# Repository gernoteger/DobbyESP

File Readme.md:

# About
DobbyESP is my own ESP8266 based IoT application for controlling things.

The name is inspired by [Dobby, the houself](http://harrypotter.wikia.com/wiki/Dobby) from Harry Potter: serves behind the scenes, but eventually develops a life on its own.

# Requirements
(mostly not yet implemented)
* [ ] enable maintainance without physical access
* [ ] Robust Wifi configuration
* [ ] OTA Updates
* [ ] Admin WebInterface
* [ ] Basic security
* [ ] MQTT for interfacing with OpenHab and crowd control
* [ ] OTA logging
* Devices + sensors
 * [ ] roller blinds / sunblinds
 * [ ] sprinkler with rain sensor
 * [ ] anything that can be switched on or off
 * [ ] Room Heating control & sensing
* make it publicly available, therefore no private acess data must be stored anywhere in version controlled files

 Since the ESP8266 is a Wifi-Only system, it doesn't lend itself well to battery powered operation; this is subject to future research
 
# Architecture

## Software Stack
* [Sming Framework](https://github.com/anakod/Sming "Sming on github")
* [rBoot] (https://github.com/raburton/esp8266 "rBoot on github") for OTA with big flash layout
* spiffs for saving connection information. I originally intended to use the original [xlfe] (https://github.com/xlfe/spiffy "original spiffy") repo; I noticed that the changes needed for Sming are not yet there, so I used [kireefco's fork] (https://github.com/kireevco/spiffy)
* and of course Espressif's SDK, currently V1.2
* Toolchain using chocolatey from sming

## Hardware

* ESP-12 and ESP-07: 4MBit/1MBit Flash, plenty of pins available, including the ADC
* Line powered: off-the-shelf USB Power modules with linear 3.3V controller
* Use Arduino relais modules to switch line: 5V form USB above come in handy, can be controlled with 3,3V from ESP
* as little as possible else

## Project Layout
The TopLevel Project contains all dependencies as git submodules, plus DobbyESP's base directory. 

# Build targets

make ...

* clean
* all

make -f Makefile-sming.mk ...
* sming-clean
* sming-all

* rboot-stuff

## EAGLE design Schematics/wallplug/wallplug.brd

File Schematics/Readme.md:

# Schematics

currently eaglepcb formatted

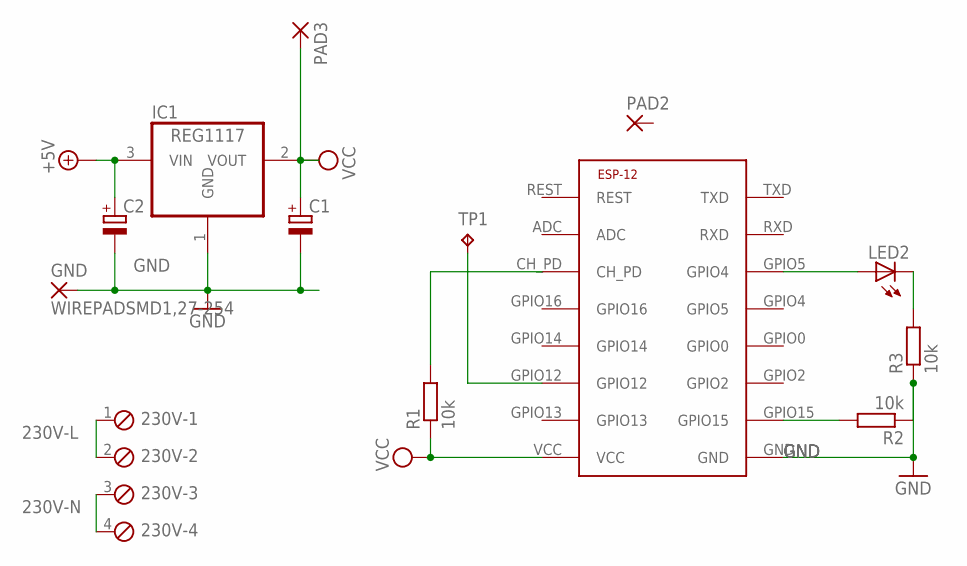
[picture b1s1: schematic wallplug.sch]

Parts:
230V: MPT4; 4POL254
C1, C2: CPOL-EUSMCC; SMC_C
ESP1: ESP-12ESP-12; ESP-12
GND: WIREPADSMD1,27-254; SMD1,27-2,54
IC1: REG1117; SOT223
LED2: LED_ESML0603; LED_SML0603
PAD2: 1,6/0,9
PAD3: SMD5; SMD2,54-5,08
R1, R2, R3: 10k; M0805; MPN LD1117S33TR
TP1: TPB1,27; B1,27

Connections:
230V-L: 230V.1, 230V.2
230V-N: 230V.3, 230V.4
+5V: C2.+, IC1.3 (VIN)
GND: C1.-, C2.-, ESP1.GND, GND.1, IC1.1 (GND), R2.1, R3.1
unnamed: ESP1.CH_PD, R1.2
unnamed: ESP1.GPIO12, TP1.TP
unnamed: ESP1.GPIO15, R2.2
unnamed: ESP1.GPIO5 (GPIO4), LED2.A
unnamed: LED2.C, R3.2
VCC: C1.+, ESP1.VCC, IC1.2 (VOUT), PAD3.1, R1.1

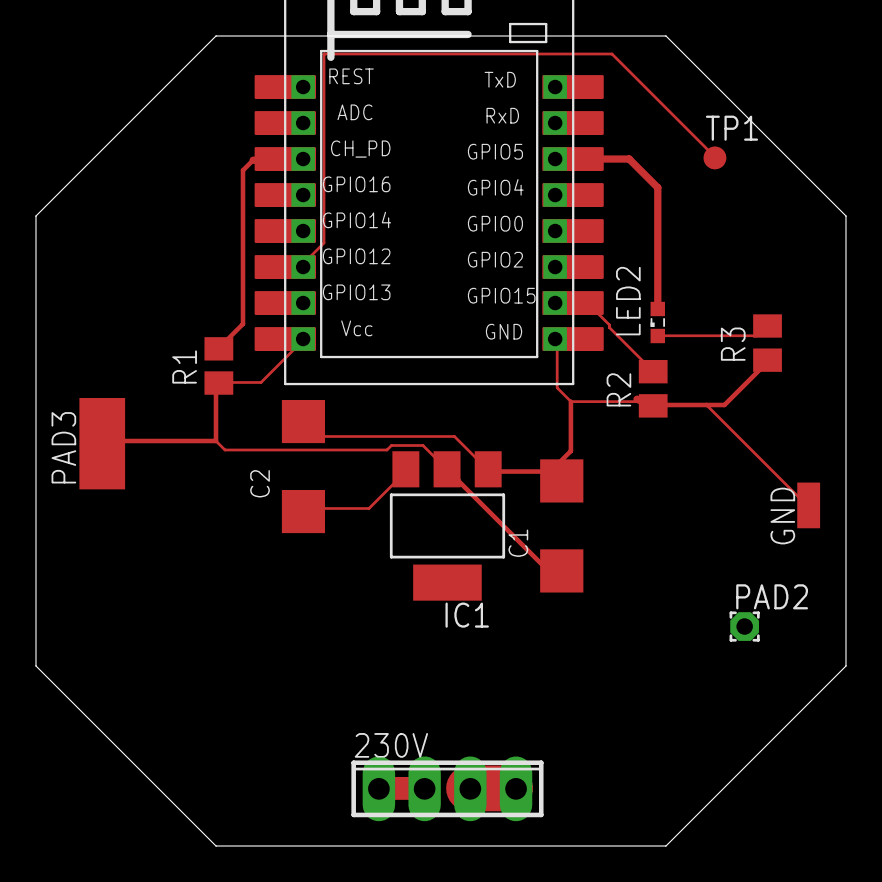
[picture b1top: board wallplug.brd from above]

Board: 2 copper layers, 45.0 x 45.0 mm, 13 parts (0 on the bottom side), 10 nets.

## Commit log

2015-09-05 initial structure
2015-09-05 build ok for spiffy
2015-09-05 starting nginx as OTA Server from make
2015-09-05 nginx working soemhow; not yet portable!
2015-09-05 putting together the new build
2015-09-05 rboot includes
2015-09-06 most errors gone
2015-09-06 removed xlfe spiffy
2015-09-06 replaced spify with precompiled version from choco build - source version here doesn't work for windows!
2015-09-06 build woks; but spiffs is formated on first boot
2015-09-06 increased spiff size to 200k, so files fit!
2015-09-06 webserver and version are working!!
2015-09-06 first successful 2-way OTA! fixing rboot-config at runtime if needed.
2015-09-06 minor updates
2015-09-06 ota for on file is working...
2015-09-06 introduced TODO list
2015-09-09 some fixes to spiff mount
2015-09-09 cleanup of repo
2015-09-09 first draft of new rboot api incorporated; still not using high level api from rboot!
2015-09-13 first somehow publishable version. Makefiles are still a mess
2015-09-13 fixedd some typos in Readme
2015-09-20 first compile
2015-09-26 first successful telnet session
2015-09-26 restructured a lot for telnet and command handling
2015-09-26 more..
2015-09-26 basic mqtt functionality; startup instable!
2015-09-26 mqtt stable now
2015-09-26 first control of led via mqtt!
2015-09-27 Button Readout working
2015-09-27 introduced basic controller
2015-09-27 minor fixes; Version re-set to 0.1-SNAPSHOT
2015-09-30 basic ADC implementation
2015-09-30 Version information extracted to class thats always built
2015-09-30 fixing version
2015-09-30 adc command supports tout and vdd33; vdd33 still not working
2015-09-30 commands use CommandHelper
2015-09-30 Temperature Controller with hysteresis implemented, not yet integrated
2015-10-02 networking. AP on/off with user button
2015-10-03 restructured project layout
2015-10-03 cleanup makefiles
2015-10-04 Restruictured towards Node/Devices classes
2015-10-05 masssive refactoring
2015-10-18 started Device Factory inside Node
2015-10-18 json parsing no longer crashes when parsing error
2015-10-18 refactoring for Messages
2015-10-18 initialization working
2015-10-18 pulled in esp_mqtt; just compiles..
2015-10-18 zwischenstand, linked nicht..
2015-10-19 mqtt new
2015-10-23 simple logging done
2015-10-27 refactored esp_mqtt inclusion
2015-10-27 mqtt spricht mit Devices
2015-11-01 simple usage system for mqtt implemented
2015-11-07 Refactored Class Tree
2015-11-07 PushButton geht so lala
2015-11-07 refactoring finalized
2015-12-14 after pause
2015-12-19 Thermostat halbwegs kontrollierbar
2015-12-19 Thermostat auf Celsius umgestellt
2016-01-04 GraylogAppender prepared, + !!! OTA functionality restored!!!
2016-01-04 first draft of Schematics
2016-01-04 first successful logs to Graylog
2016-01-04 basic logging working; just LOG_INFO implemented..
2016-01-05 fix for host in GELF message
2016-01-09 update läuft, sonst chaos
2016-01-16 Version für erste Installation
2016-01-20 eingebaute Version
2016-01-24 build cleanup: startwith rboot
2016-01-24 updating submodules
2016-01-24 changes sming submodule to dobby_test1 branch
2016-01-24 cleaning spiffy
2016-01-25 makefiles adjusted to linux
2016-01-25 changed serial to linux
2016-01-25 fixed makefiles; still dependency issues
2016-01-25 fixed mor submodules
2016-01-30 first changes
2016-01-30 include fehler gelöst
2016-01-31 adopted mqtt to enable compile+link
2016-01-31 spiffy also working
2016-01-31 terminal angepasst
2016-01-31 ignoring db.txt (=my make debug output)
2016-02-20 update von dobby + submodule commit von allen
2016-04-09 device creation hardcoded Teil1
2016-04-09 directly controlled button working; OTA still a mess!!
2016-04-09 tried use of ICACHE_FLASH_ATTR; no effect on RAM whatsoever
2016-04-10 describe testing
2017-05-21 updated docs
2017-07-05 created readme for schematics
